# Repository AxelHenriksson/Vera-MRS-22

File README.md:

# Vera-MRS-22

Styrkort för motorrummet i Vera III

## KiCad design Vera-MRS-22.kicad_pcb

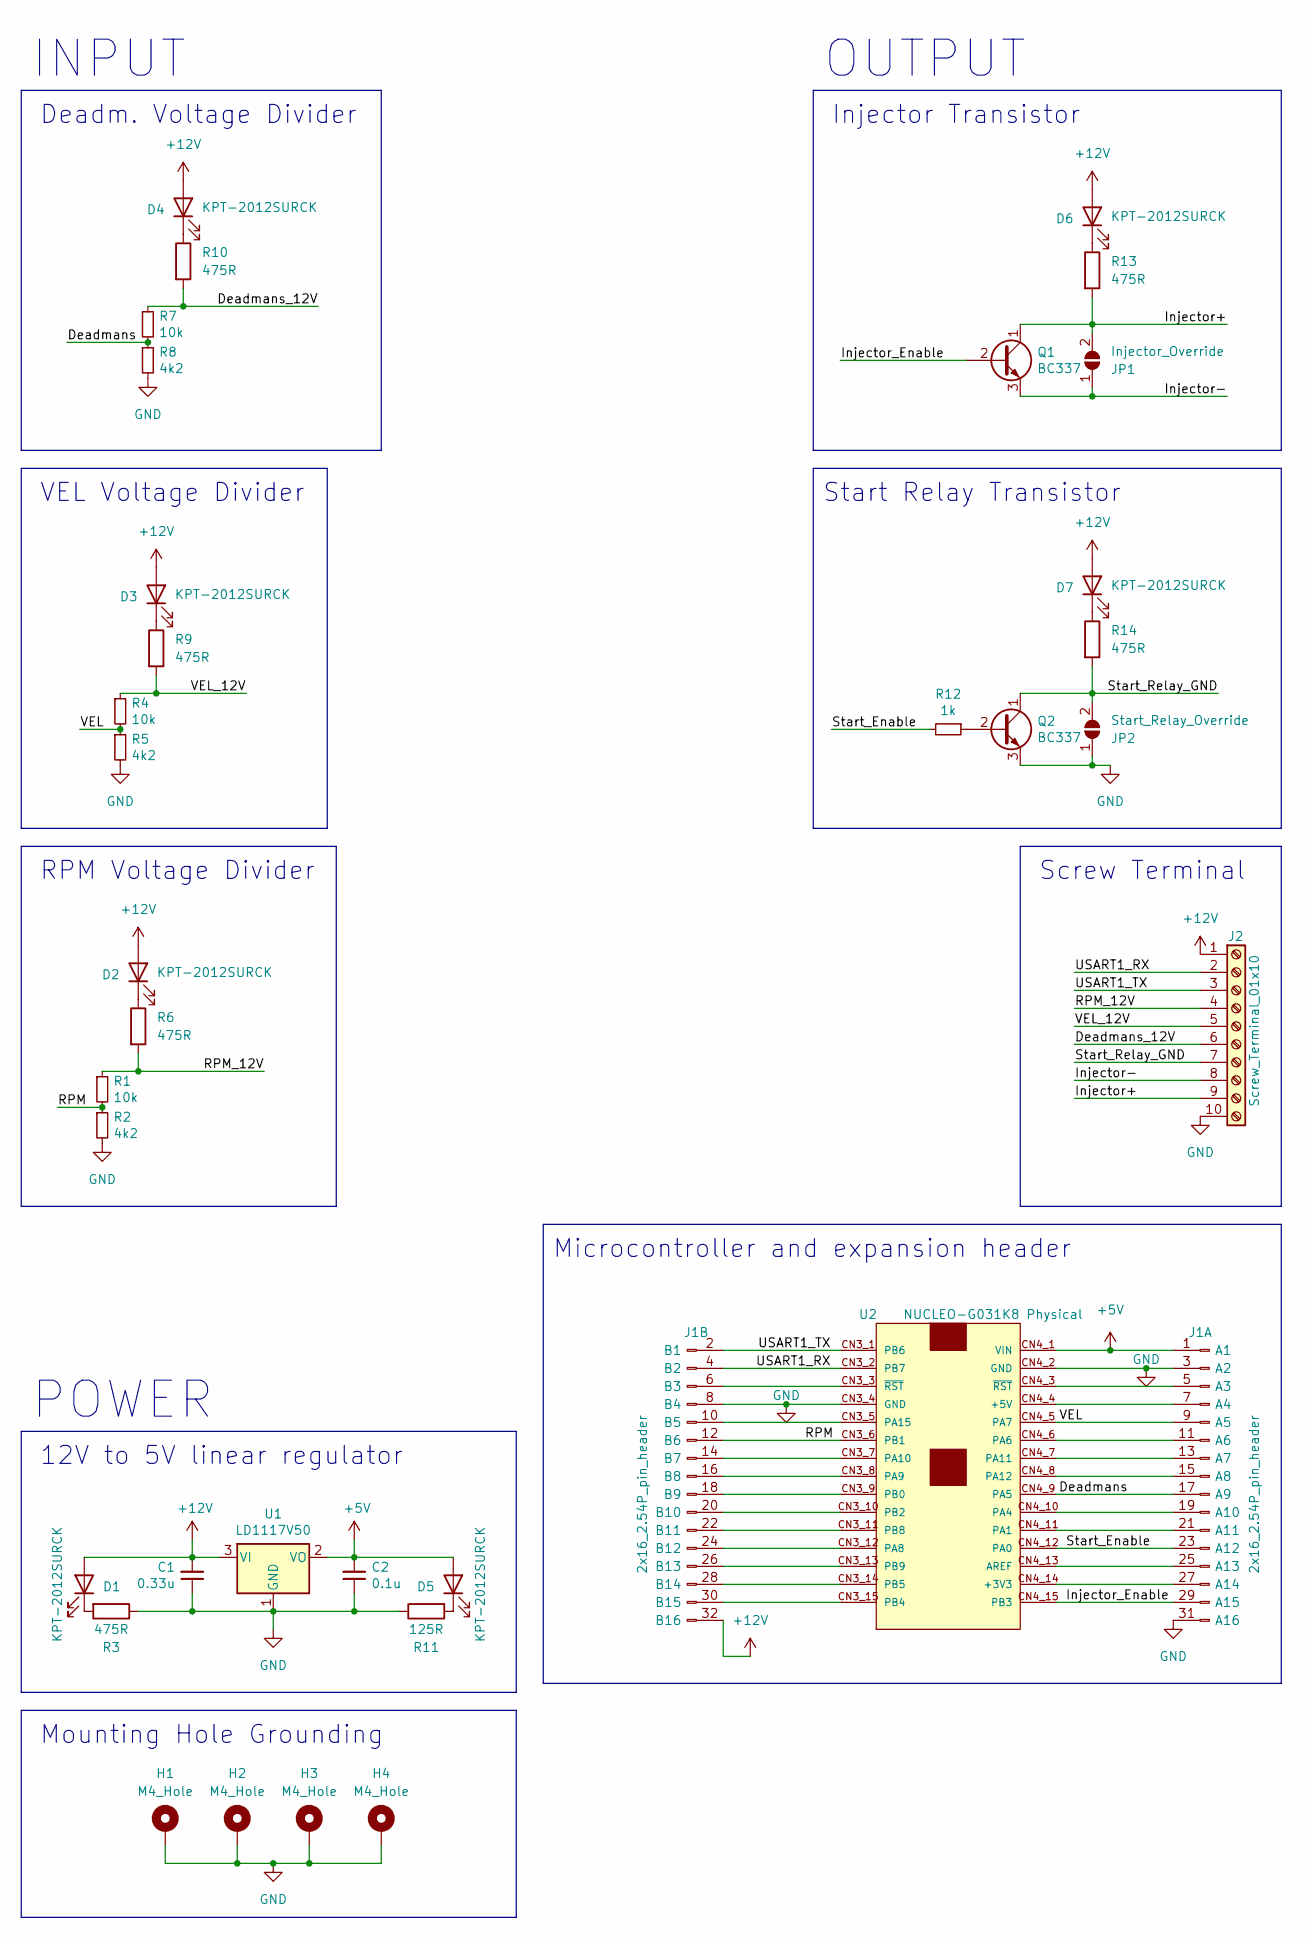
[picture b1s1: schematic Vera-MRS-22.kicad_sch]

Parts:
C1: 0.33u; C_1206_3216Metric_Pad1.33x1.80mm_HandSolder
C2: 0.1u; C_1206_3216Metric_Pad1.33x1.80mm_HandSolder
D1, D2, D3, D4, D5, D6, D7: KPT-2012SURCK; LED_0805_2012Metric_Pad1.15x1.40mm_HandSolder
H1, H2, H3, H4: M4_Hole; MountingHole_4.3mm_M4_ISO14580_Pad
J1: 2x16_2.54P_pin_header; PinHeader_2x16_P2.54mm_Vertical
J2: Screw_Terminal_01x10; TerminalBlock_Phoenix_MPT-0,5-10-2.54_1x10_P2.54mm_Horizont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
JP1: Injector_Override; SolderJumper-2_P1.3mm_Open_TrianglePad1.0x1.5mm
JP2: Start_Relay_Override; SolderJumper-2_P1.3mm_Open_TrianglePad1.0x1.5mm
Q1, Q2: BC337; TO-92_Inline
R1, R4, R7: 10k; R_Axial_DIN0207_L6.3mm_D2.5mm_P10.16mm_Horizontal
R2, R5, R8: 4k2; R_Axial_DIN0207_L6.3mm_D2.5mm_P10.16mm_Horizontal
R3, R6, R9, R10, R13, R14: 475R; R_1206_3216Metric_Pad1.30x1.75mm_HandSolder
R11: 125R; R_1206_3216Metric_Pad1.30x1.75mm_HandSolder
R12: 1k; R_Axial_DIN0207_L6.3mm_D2.5mm_P10.16mm_Horizontal
U1: LD1117V50; TO-220-3_Horizontal_TabDown
U2: NUCLEO-G031K8 Physical; NUCLEO_32; PARTREV N/A

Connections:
+5V: C2.2, D5.2 (A), J1.1 (A1), U1.2 (VO), U2.CN4_1 (VIN)
+12V: C1.2, D1.2 (A), D2.2 (A), D3.2 (A), D4.2 (A), D6.2 (A), D7.2 (A), J1.32 (B16), J2.1, U1.3 (VI)
/Deadmans: J1.17 (A9), R7.2, R8.1, U2.CN4_9 (PA5)
/Deadmans_12V: J2.6, R7.1, R10.2
/Injector+: J2.9, JP1.2 (B), Q1.1 (C), R13.2
/Injector-: J2.8, JP1.1 (A), Q1.3 (E)
/Injector_Enable: J1.29 (A15), Q1.2 (B), U2.CN4_15 (PB3)
/RPM: J1.12 (B6), R1.2, R2.1, U2.CN3_6 (PB1)
/RPM_12V: J2.4, R1.1, R6.2
/Start_Enable: J1.23 (A12), R12.2, U2.CN4_12 (PA0)
/Start_Relay_GND: J2.7, JP2.2 (B), Q2.1 (C), R14.2
/USART1_RX: J1.4 (B2), J2.2, U2.CN3_2 (PB7)
/USART1_TX: J1.2 (B1), J2.3, U2.CN3_1 (PB6)
/VEL: J1.9 (A5), R4.2, R5.1, U2.CN4_5 (PA7)
/VEL_12V: J2.5, R4.1, R9.2
GND: C1.1, C2.1, H1.1, H2.1, H3.1, H4.1, J1.3 (A2), J1.8 (B4), J1.31 (A16), J2.10, JP2.1 (A), Q2.3 (E), R2.2, R3.1, R5.2, R8.2, R11.1, U1.1 (GND), U2.CN3_4 (GND), U2.CN4_2 (GND)
unnamed: D1.1 (K), R3.2
unnamed: D2.1 (K), R6.1
unnamed: D3.1 (K), R9.1
unnamed: D4.1 (K), R10.1
unnamed: D5.1 (K), R11.2
unnamed: D6.1 (K), R13.1
unnamed: D7.1 (K), R14.1
unnamed: J1.5 (A3), U2.CN4_3 (~RST)
unnamed: J1.6 (B3), U2.CN3_3 (~RST)
unnamed: J1.7 (A4), U2.CN4_4 (+5V)
unnamed: J1.10 (B5), U2.CN3_5 (PA15)
unnamed: J1.11 (A6), U2.CN4_6 (PA6)
unnamed: J1.13 (A7), U2.CN4_7 (PA11)
unnamed: J1.14 (B7), U2.CN3_7 (PA10)
unnamed: J1.15 (A8), U2.CN4_8 (PA12)
unnamed: J1.16 (B8), U2.CN3_8 (PA9)
unnamed: J1.18 (B9), U2.CN3_9 (PB0)
unnamed: J1.19 (A10), U2.CN4_10 (PA4)
unnamed: J1.20 (B10), U2.CN3_10 (PB2)
unnamed: J1.21 (A11), U2.CN4_11 (PA1)
unnamed: J1.22 (B11), U2.CN3_11 (PB8)
unnamed: J1.24 (B12), U2.CN3_12 (PA8)
unnamed: J1.25 (A13), U2.CN4_13 (AREF)
unnamed: J1.26 (B13), U2.CN3_13 (PB9)
unnamed: J1.27 (A14), U2.CN4_14 (+3V3)
unnamed: J1.28 (B14), U2.CN3_14 (PB5)
unnamed: J1.30 (B15), U2.CN3_15 (PB4)
unnamed: Q2.2 (B), R12.1

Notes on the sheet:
Microcontroller and expansion header
INPUT
Screw Terminal
VEL Voltage Divider
12V to 5V linear regulator
Mounting Hole Grounding
Start Relay Transistor
OUTPUT
Injector Transistor
Deadm. Voltage Divider
RPM Voltage Divider
POWER

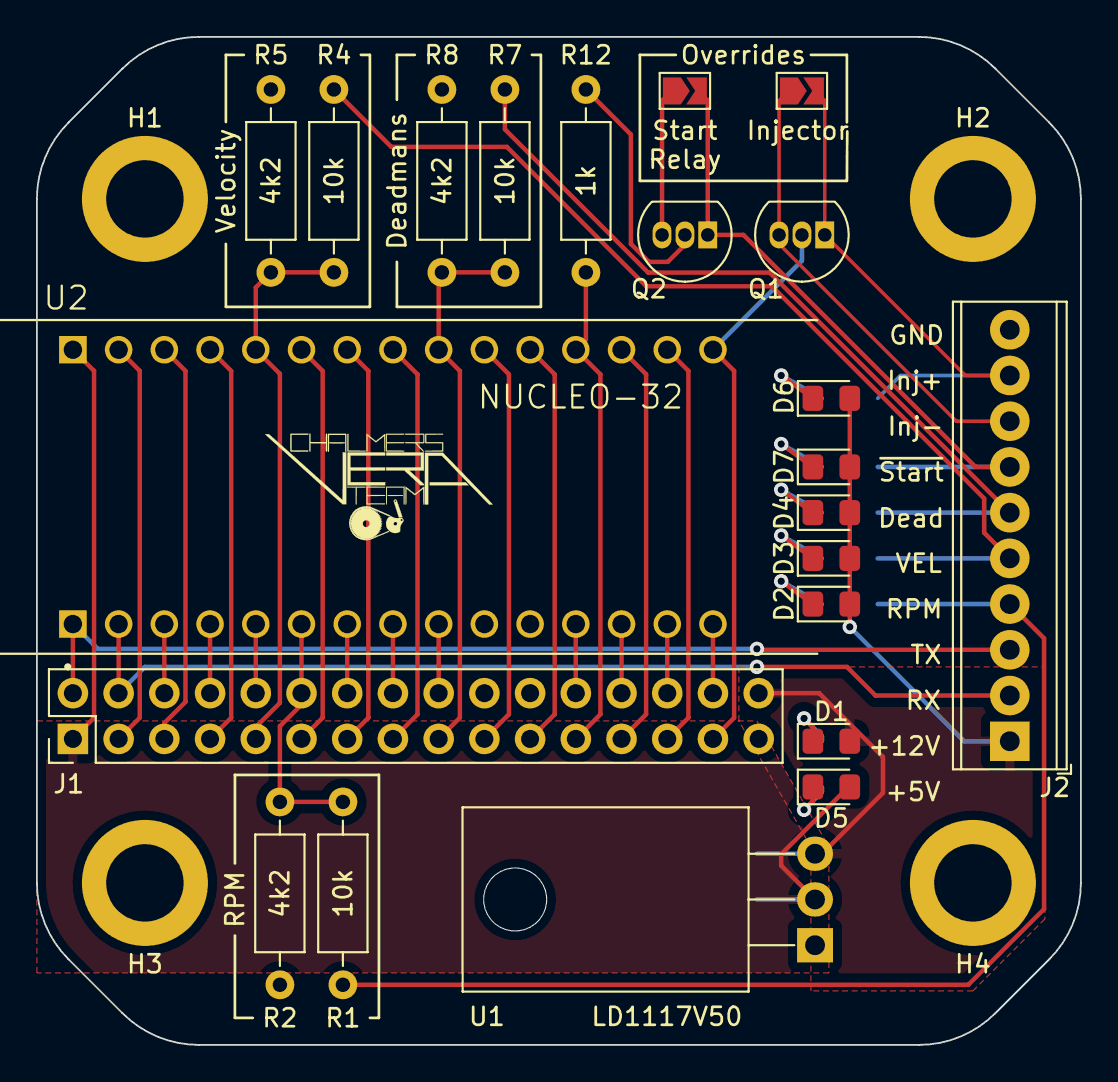
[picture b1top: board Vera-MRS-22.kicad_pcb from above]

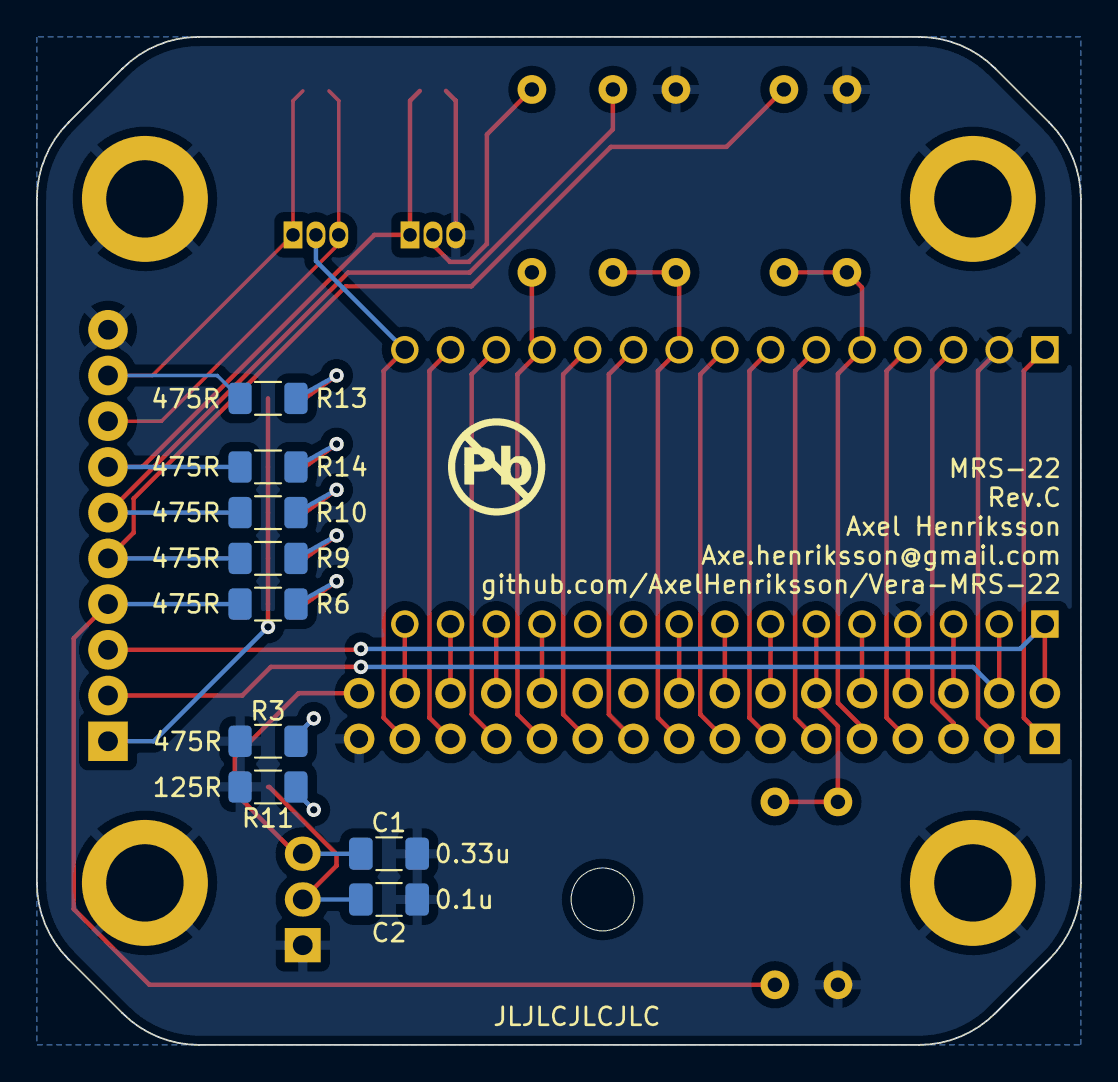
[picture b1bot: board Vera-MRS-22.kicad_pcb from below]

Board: 2 copper layers, 58.0 x 56.0 mm, 35 parts (9 on the bottom side), 44 nets.

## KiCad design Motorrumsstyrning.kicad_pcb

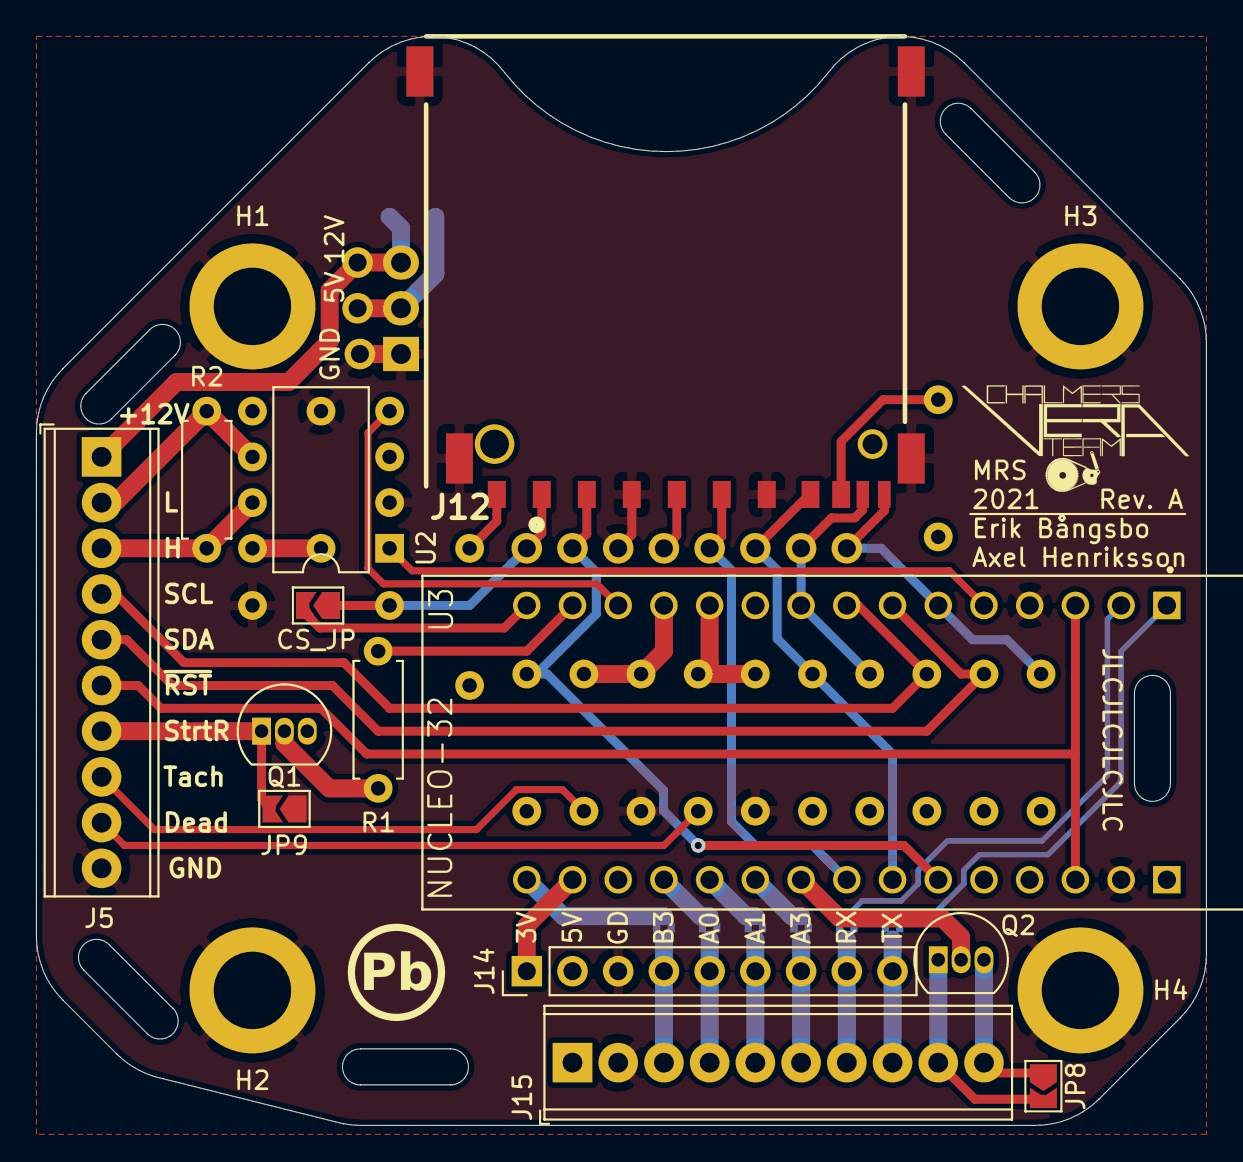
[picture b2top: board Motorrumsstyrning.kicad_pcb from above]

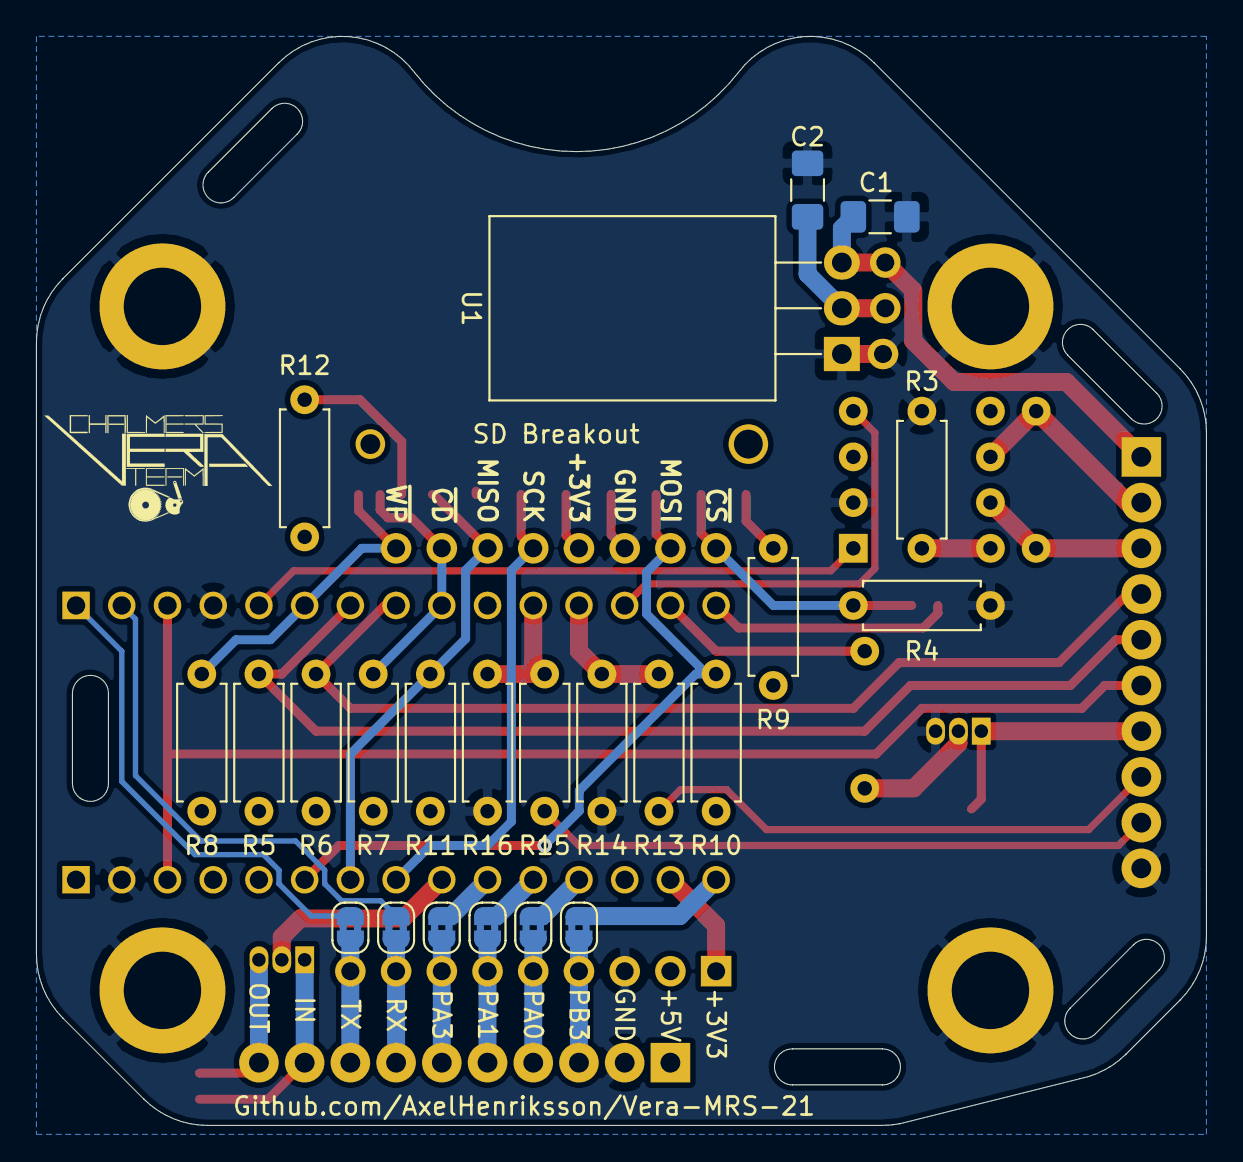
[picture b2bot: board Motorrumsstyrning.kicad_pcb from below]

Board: 4 copper layers, 65.0 x 60.5 mm, 51 parts (23 on the bottom side), 43 nets.

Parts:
C1: 0.33u; C_1206_3216Metric_Pad1.42x1.75mm_HandSolder
C2: 0.1u; C_1206_3216Metric_Pad1.42x1.75mm_HandSolder
H1, H2, H3, H4: M4_Hole; MountingHole_4.3mm_M4_ISO14580_Pad
J1, J2, J3, J4, J6, J7, J8, J9, J10, J11, J13: Jumper; THT_Jumper
J5, J15: Screw_Terminal_01x10; TerminalBlock_Phoenix_MPT-0,5-10-2.54_1x10_P2.54mm_Horizont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
J12: SD_Card_Connector; 2041021-3_2
J14: Conn_01x09; PinHeader_1x09_P2.54mm_Vertical
JP1: CS_Jumper; SolderJumper-2_P1.3mm_Open_TrianglePad1.0x1.5mm
JP2, JP3, JP4, JP5, JP6, JP7: SolderJumper_2_Bridged; SolderJumper-2_P1.3mm_Bridged2Bar_RoundedPad1.0x1.5mm
JP8: Injector_Override; SolderJumper-2_P1.3mm_Open_TrianglePad1.0x1.5mm
JP9: Start_Relay_Override; SolderJumper-2_P1.3mm_Open_TrianglePad1.0x1.5mm
Q1, Q2: BC337; TO-92_Inline
R1, R5, R6: 1k; R_Axial_DIN0207_L6.3mm_D2.5mm_P7.62mm_Horizontal
R2: 120R; R_Axial_DIN0207_L6.3mm_D2.5mm_P7.62mm_Horizontal
R3: R_Small; R_Axial_DIN0207_L6.3mm_D2.5mm_P7.62mm_Horizontal
R4, R7, R8, R9, R10, R11, R12: 50k; R_Axial_DIN0207_L6.3mm_D2.5mm_P7.62mm_Horizontal
R13, R15: 4k2; R_Axial_DIN0207_L6.3mm_D2.5mm_P7.62mm_Horizontal
R14, R16: 10k; R_Axial_DIN0207_L6.3mm_D2.5mm_P7.62mm_Horizontal
U1: LM1084-5.0; TO-220-3_Horizontal_TabDown
U2: MCP2551-I-P; DIP-8_W7.62mm
U3: NUCLEO-F303K8; NUCLEO_32

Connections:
+3V3: J4.1, J12.4, J14.1, R5.1, R6.1, R7.1, R8.1, R9.1, R10.1, R11.1, R12.1, U3.CN4_14
+5V: C2.2, J2.1, J14.2, J15.1, U1.2, U2.3, U3.CN4_4
+12V: C1.2, J1.1, J5.1, U1.3
/CANH: J5.3, R2.1, U2.7
/CANL: J5.2, R2.2, U2.6
/CAN_RX: U2.4, U3.CN3_13
/CAN_TX: U2.1, U3.CN3_5
/Deadmans: R15.2, R16.1, U3.CN3_11
/Deadmans_12V: J5.9, R15.1
/I2C1_SCL: J5.4, R6.2, U3.CN3_8
/I2C1_SDA: J5.5, R5.2, U3.CN3_7
/Injector_Enable: Q2.2, U3.CN4_9
/Injector_IN: J15.9, JP8.2, Q2.1
/Injector_OUT: J15.10, JP8.1, Q2.3
/PA0: JP3.1, U3.CN4_12
/PA1: JP4.1, U3.CN4_11
/PA3: JP5.1, U3.CN4_10
/PB3: JP2.1, U3.CN4_15
/PB4: JP1.2, U3.CN3_15
/SPI1_MISO: J11.1, J12.7, R11.2, U3.CN4_7
/SPI1_MOSI: J9.1, J12.2, R10.2, U3.CN4_6
/SPI1_SCK: J10.1, J12.5, U3.CN4_8
/Start_Enable: R1.2, U3.CN3_14
/Start_Relay_GND: J5.7, JP9.2, Q1.1
/Tach_12V: J5.8, R13.1
/Tachometer: R13.2, R14.1, U3.CN3_12
/USART1_RX: JP6.1, U3.CN3_2
/USART1_TX: JP7.1, U3.CN3_1
/~CD: J6.1, J12.10, R7.2, U3.CN3_9
/~CS: J8.1, J12.1, JP1.1, R4.1
/~RST: J5.6, U3.CN3_3, U3.CN4_3
/~WP: J7.1, J12.11, R8.2, U3.CN3_6
GND: C1.1, C2.1, H1.1, H2.1, H3.1, H4.1, J3.1, J5.10, J12.3, J12.6, J12.12, J12.13, J12.14, J12.15, J13.1, J14.3, J15.2, JP9.1, Q1.3, R3.1, R4.2, R14.2, R16.2, U1.1, U2.2, U3.CN3_4, U3.CN4_2
unnamed: J12.8, R12.2
unnamed: J12.9, R9.2
unnamed: J14.4, J15.3, JP2.2
unnamed: J14.5, J15.4, JP3.2
unnamed: J14.6, J15.5, JP4.2
unnamed: J14.7, J15.6, JP5.2
unnamed: J14.8, J15.7, JP6.2
unnamed: J14.9, J15.8, JP7.2
unnamed: Q1.2, R1.1
unnamed: R3.2, U2.8

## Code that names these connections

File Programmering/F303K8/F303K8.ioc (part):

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Mcu.Name=STM32F303K(6-8)Tx
Mcu.Package=LQFP32
Mcu.UserName=STM32F303K8Tx
PA0.GPIOParameters=GPIO_Label
PA0.GPIO_Label=PA0
PA0.Signal=GPIO_Output
PA1.GPIOParameters=GPIO_Label
PA1.GPIO_Label=PA1
PA1.Signal=GPIO_Output
PA10.Mode=Asynchronous
PA10.Signal=USART1_RX
PA11.Mode=CAN_Activate
PA11.Signal=CAN_RX
PA12.Mode=CAN_Activate
PA12.Signal=CAN_TX
PA13.GPIOParameters=GPIO_Label
PA13.GPIO_Label=SWDIO
PA13.Mode=Serial_Wire
PA13.Signal=SYS_JTMS-SWDIO
PA14.GPIOParameters=GPIO_Label
PA14.GPIO_Label=SWCLK
PA14.Mode=Serial_Wire
PA14.Signal=SYS_JTCK-SWCLK
PA15.GPIOParameters=GPIO_Label
PA15.GPIO_Label=VCP_RX
PA15.Mode=Asynchronous
PA15.Signal=USART2_RX
PA2.GPIOParameters=GPIO_Label
PA2.GPIO_Label=VCP_TX
PA2.Mode=Asynchronous
PA2.Signal=USART2_TX
PA3.GPIOParameters=GPIO_Label
PA3.GPIO_Label=PA3
PA3.Signal=GPIO_Output
PA4.GPIOParameters=GPIO_Label
PA4.GPIO_Label=Injector_Enable
PA4.Signal=GPIO_Output
PA5.Mode=Full_Duplex_Master
PA5.Signal=SPI1_SCK
PA6.Mode=Full_Duplex_Master
PA6.Signal=SPI1_MISO
PA7.Mode=Full_Duplex_Master
PA7.Signal=SPI1_MOSI
PA8.GPIOParameters=GPIO_Label
PA8.GPIO_Label=Tachometer
PA8.Signal=GPIO_Input
PA9.Mode=Asynchronous
PA9.Signal=USART1_TX
PB0.GPIOParameters=GPIO_Label
PB0.GPIO_Label=NWrite_Protect
PB0.Signal=GPIO_Output
PB1.GPIOParameters=GPIO_Label
PB1.GPIO_Label=NCard_Detect
PB1.Signal=GPIO_Input
PB3.GPIOParameters=GPIO_Label
PB3.GPIO_Label=PB3
PB3.Signal=GPIO_Output
PB4.GPIOParameters=GPIO_Label
PB4.GPIO_Label=PB4
PB4.Signal=GPIO_Output
PB5.GPIOParameters=GPIO_Label
PB5.GPIO_Label=Start_Enable
PB5.Signal=GPIO_Output
PB6.Mode=I2C
PB6.Signal=I2C1_SCL
PB7.Mode=I2C
PB7.Signal=I2C1_SDA
PF0\ /\ OSC_IN.GPIOParameters=GPIO_Label
PF0\ /\ OSC_IN.GPIO_Label=MCO
PF0\ /\ OSC_IN.Mode=HSE-External-Clock-Source
PF0\ /\ OSC_IN.Signal=RCC_OSC_IN
PF1\ /\ OSC_OUT.GPIOParameters=GPIO_Label
PF1\ /\ OSC_OUT.GPIO_Label=Deadmans
PF1\ /\ OSC_OUT.Signal=GPIO_Input
RCC.HSEPLLFreq_Value=8000000
RCC.HSE_VALUE=8000000
RCC.SYSCLKFreq_VALUE=8000000
board=NUCLEO-F303K8
boardIOC=true

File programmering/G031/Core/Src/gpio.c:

/* USER CODE BEGIN Header */
/**
  ******************************************************************************
  * @file    gpio.c
  * @brief   This file provides code for the configuration
  *          of all used GPIO pins.
  ******************************************************************************
  * @attention
  *
  * Copyright (c) 2022 STMicroelectronics.
  * All rights reserved.
  *
  * This software is licensed under terms that can be found in the LICENSE file
  * in the root directory of this software component.
  * If no LICENSE file comes with this software, it is provided AS-IS.
  *
  ******************************************************************************
  */
/* USER CODE END Header */

/* Includes ------------------------------------------------------------------*/
#include "gpio.h"

/* USER CODE BEGIN 0 */

/* USER CODE END 0 */

/*----------------------------------------------------------------------------*/
/* Configure GPIO                                                             */
/*----------------------------------------------------------------------------*/
/* USER CODE BEGIN 1 */

/* USER CODE END 1 */

/** Configure pins as
        * Analog
        * Input
        * Output
        * EVENT_OUT
        * EXTI
        * Free pins are configured automatically as Analog (this feature is enabled through
        * the Code Generation settings)
*/
void MX_GPIO_Init(void)
{

  GPIO_InitTypeDef GPIO_InitStruct = {0};

  /* GPIO Ports Clock Enable */
  __HAL_RCC_GPIOB_CLK_ENABLE();
  __HAL_RCC_GPIOC_CLK_ENABLE();
  __HAL_RCC_GPIOF_CLK_ENABLE();
  __HAL_RCC_GPIOA_CLK_ENABLE();

  /*Configure GPIO pin Output Level */
  HAL_GPIO_WritePin(Start_Enable_GPIO_Port, Start_Enable_Pin, GPIO_PIN_RESET);

  /*Configure GPIO pin Output Level */
  HAL_GPIO_WritePin(LD3_GPIO_Port, LD3_Pin, GPIO_PIN_RESET);

  /*Configure GPIO pin Output Level */
  HAL_GPIO_WritePin(Injector_Enable_GPIO_Port, Injector_Enable_Pin, GPIO_PIN_SET);

  /*Configure GPIO pins : PB9 PB0 PB2 PB4
                           PB5 PB8 */
  GPIO_InitStruct.Pin = GPIO_PIN_9|GPIO_PIN_0|GPIO_PIN_2|GPIO_PIN_4
                          |GPIO_PIN_5|GPIO_PIN_8;
  GPIO_InitStruct.Mode = GPIO_MODE_ANALOG;
  GPIO_InitStruct.Pull = GPIO_NOPULL;
  HAL_GPIO_Init(GPIOB, &GPIO_InitStruct);

  /*Configure GPIO pin : PF2 */
  GPIO_InitStruct.Pin = GPIO_PIN_2;
  GPIO_InitStruct.Mode = GPIO_MODE_ANALOG;
  GPIO_InitStruct.Pull = GPIO_NOPULL;
  HAL_GPIO_Init(GPIOF, &GPIO_InitStruct);

  /*Configure GPIO pin : PtPin */
  GPIO_InitStruct.Pin = Start_Enable_Pin;
  GPIO_InitStruct.Mode = GPIO_MODE_OUTPUT_PP;
  GPIO_InitStruct.Pull = GPIO_NOPULL;
  GPIO_InitStruct.Speed = GPIO_SPEED_FREQ_LOW;
  HAL_GPIO_Init(Start_Enable_GPIO_Port, &GPIO_InitStruct);

  /*Configure GPIO pins : PA1 PA4 PA6 PA8
                           PA9 PA10 PA11 PA12
                           PA15 */
  GPIO_InitStruct.Pin = GPIO_PIN_1|GPIO_PIN_4|GPIO_PIN_6|GPIO_PIN_8
                          |GPIO_PIN_9|GPIO_PIN_10|GPIO_PIN_11|GPIO_PIN_12
                          |GPIO_PIN_15;
  GPIO_InitStruct.Mode = GPIO_MODE_ANALOG;
  GPIO_InitStruct.Pull = GPIO_NOPULL;
  HAL_GPIO_Init(GPIOA, &GPIO_InitStruct);

  /*Configure GPIO pin : PtPin */
  GPIO_InitStruct.Pin = Deadmans_Pin;
  GPIO_InitStruct.Mode = GPIO_MODE_IT_RISING_FALLING;
  GPIO_InitStruct.Pull = GPIO_PULLUP;
  HAL_GPIO_Init(Deadmans_GPIO_Port, &GPIO_InitStruct);

  /*Configure GPIO pin : PtPin */
  GPIO_InitStruct.Pin = VEL_Pin;
  GPIO_InitStruct.Mode = GPIO_MODE_IT_FALLING;
  GPIO_InitStruct.Pull = GPIO_PULLUP;
  HAL_GPIO_Init(VEL_GPIO_Port, &GPIO_InitStruct);

  /*Configure GPIO pin : PtPin */
  GPIO_InitStruct.Pin = RPM_Pin;
  GPIO_InitStruct.Mode = GPIO_MODE_IT_FALLING;
  GPIO_InitStruct.Pull = GPIO_PULLUP;
  HAL_GPIO_Init(RPM_GPIO_Port, &GPIO_InitStruct);

  /*Configure GPIO pin : PtPin */
  GPIO_InitStruct.Pin = LD3_Pin;
  GPIO_InitStruct.Mode = GPIO_MODE_OUTPUT_PP;
  GPIO_InitStruct.Pull = GPIO_NOPULL;
  GPIO_InitStruct.Speed = GPIO_SPEED_FREQ_LOW;
  HAL_GPIO_Init(LD3_GPIO_Port, &GPIO_InitStruct);

  /*Configure GPIO pin : PtPin */
  GPIO_InitStruct.Pin = Injector_Enable_Pin;
  GPIO_InitStruct.Mode = GPIO_MODE_OUTPUT_PP;
  GPIO_InitStruct.Pull = GPIO_NOPULL;
  GPIO_InitStruct.Speed = GPIO_SPEED_FREQ_LOW;
  HAL_GPIO_Init(Injector_Enable_GPIO_Port, &GPIO_InitStruct);

  /* EXTI interrupt init*/
  HAL_NVIC_SetPriority(EXTI0_1_IRQn, 0, 0);
  HAL_NVIC_EnableIRQ(EXTI0_1_IRQn);

  HAL_NVIC_SetPriority(EXTI4_15_IRQn, 0, 0);
  HAL_NVIC_EnableIRQ(EXTI4_15_IRQn);

}

/* USER CODE BEGIN 2 */

/* USER CODE END 2 */

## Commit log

2021-04-26 Board outline and mounting holes added
2021-05-02 Incremental update
2021-05-06 Added components in schematic
2021-05-24 Added symbols, worked on schematic and PCB
2021-05-25 Large PCB first design
2021-05-25 Added small logo, moved parts
2021-05-26 Added Testpoints, Ziptie slots, I2C pull-ups
2021-05-26 Recommit
2021-05-26 Moved terminal block, Added Testpoint labels
2021-06-01 Added SD breakout labels and Vera logo on back
2021-06-12 CAN tranciever o transistor
2021-06-21 Added programing folder
2021-06-21 progg
2021-06-21 Added to PCB
2021-07-25 First complete draft
2021-08-11 Vidareutveckling
2021-08-11 Removed old code, generated new for F303K8
2021-08-14 Fixed Silkscreen
2021-09-07 Finalization and Gerber generation
2021-09-09 Added Override jumpers, regenerated gerbers, ordered PCB
2022-05-15 Removed Files
2022-05-15 New Initial Commit
2022-05-18 Finished RevB and sent for manufature
2022-05-20 Rev.C
    Added LEDs
2022-06-19 VEL, RPM och startmotorsignal programmerat
